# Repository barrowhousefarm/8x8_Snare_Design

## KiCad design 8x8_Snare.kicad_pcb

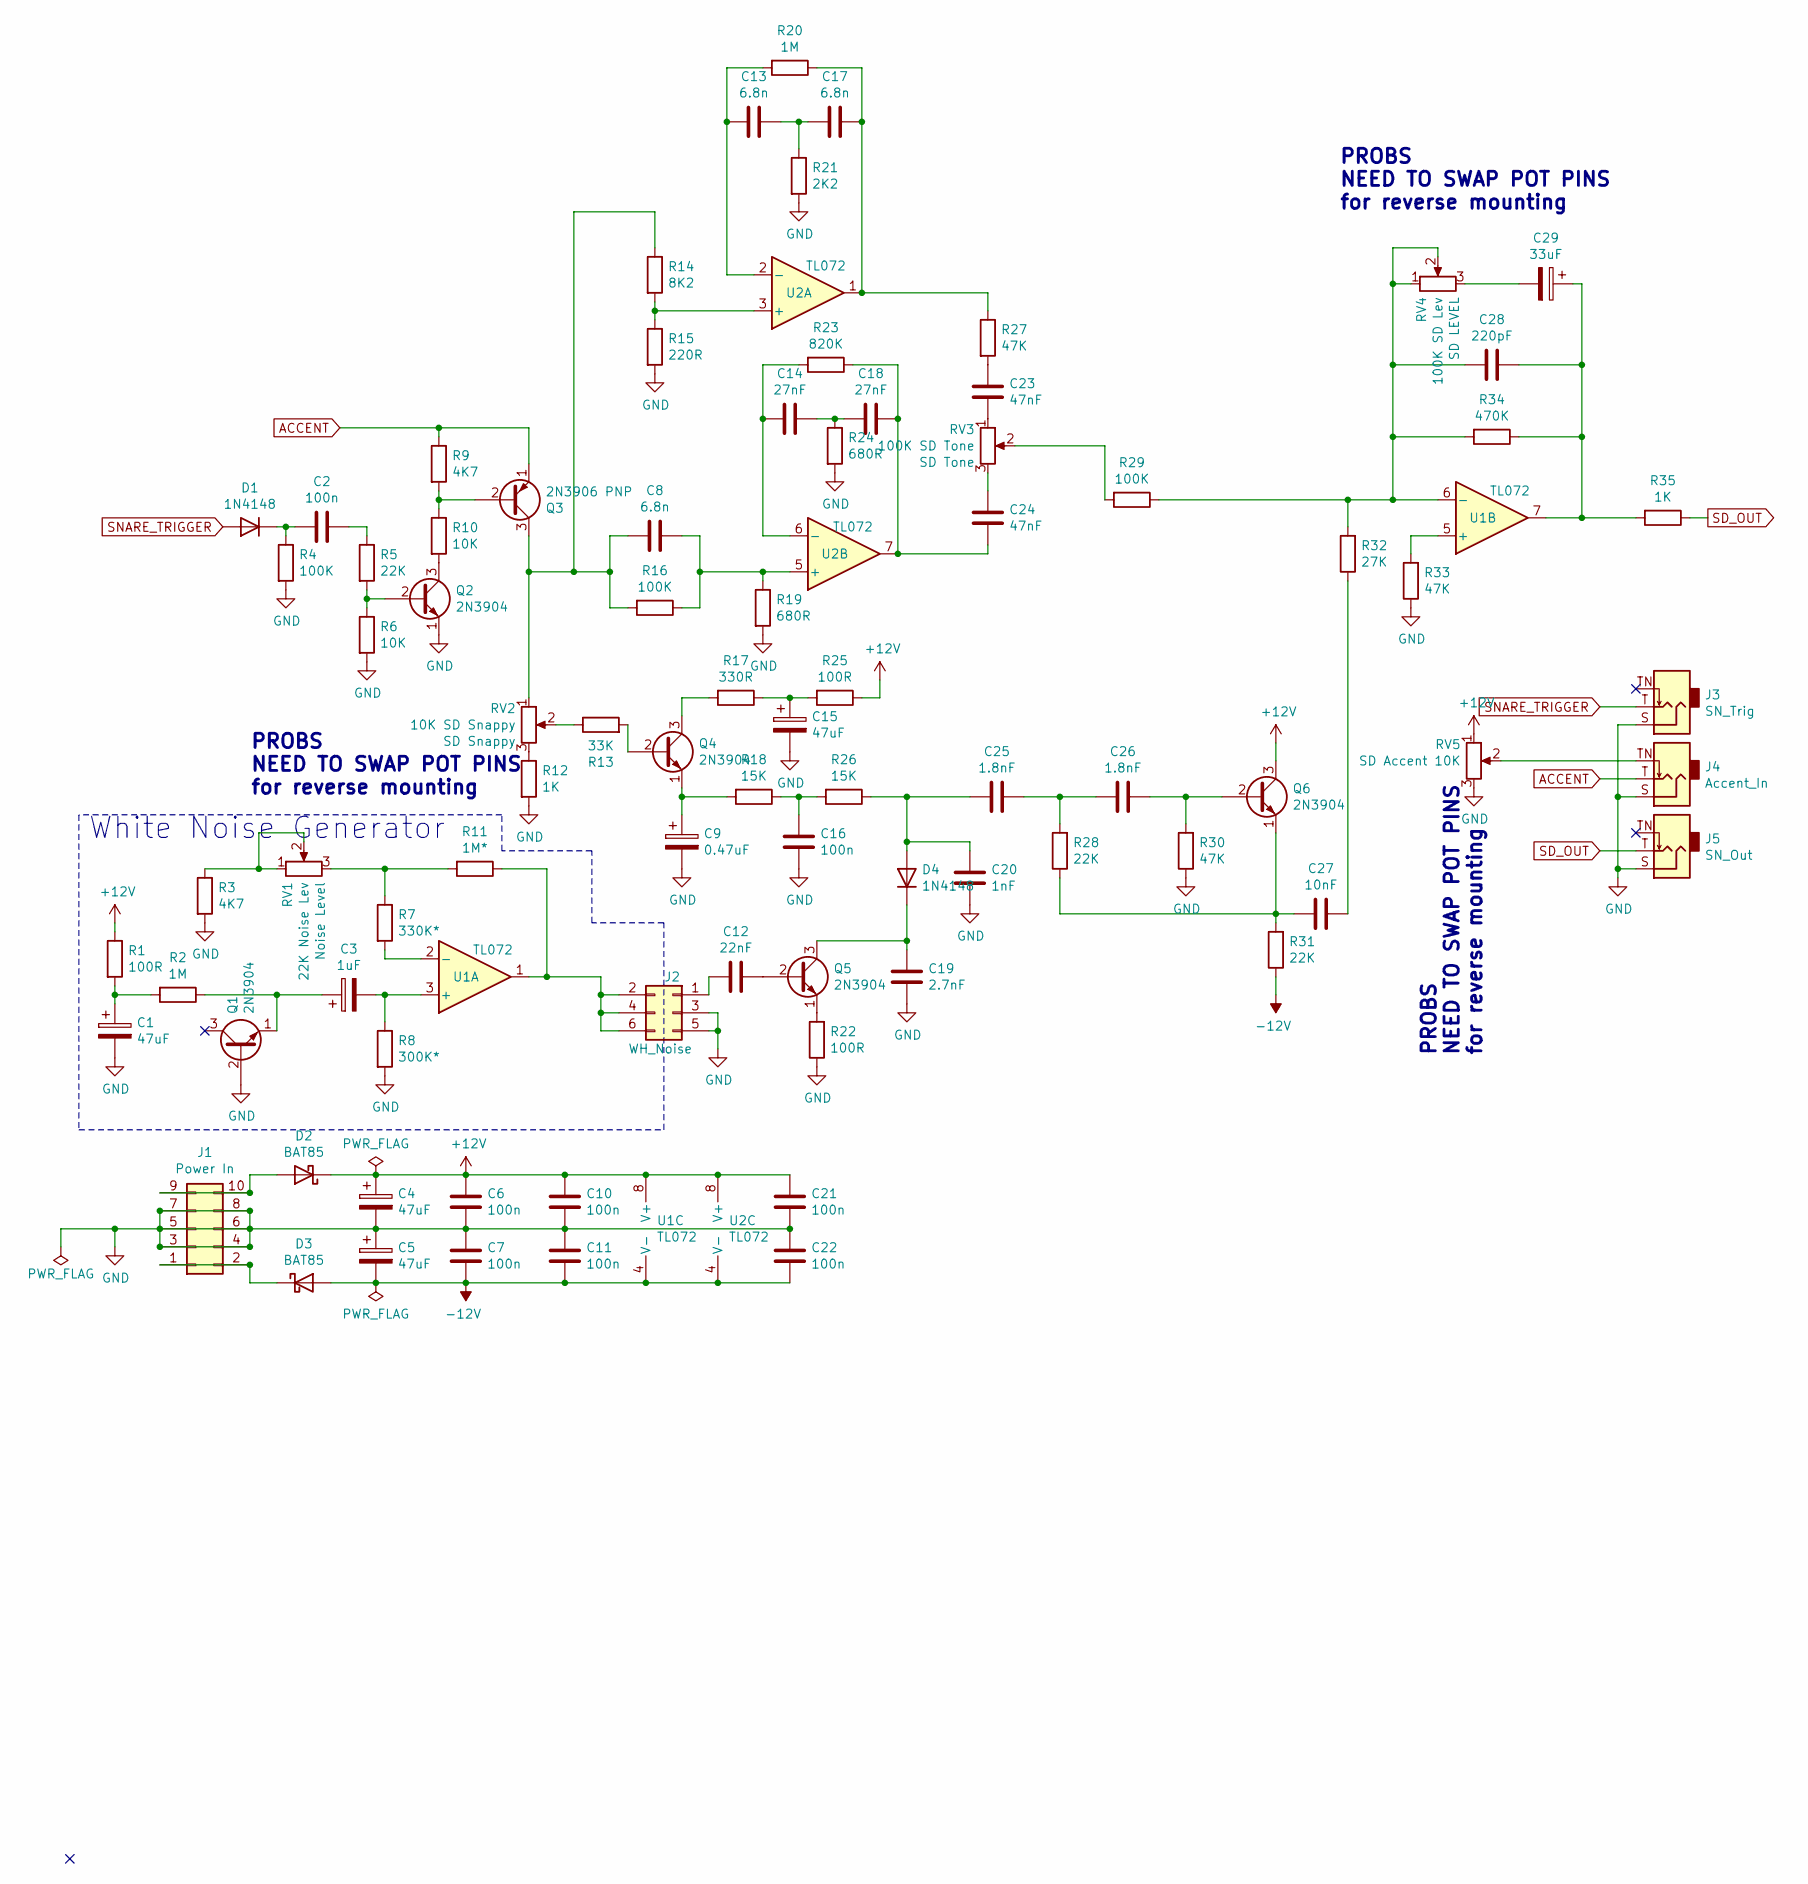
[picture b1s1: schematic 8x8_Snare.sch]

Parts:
C1, C4, C5, C15: 47uF; CP_Radial_D6.3mm_P2.50mm
C2, C6, C7, C10, C11, C16, C21, C22: 100n; C_1206_3216Metric_Pad1.33x1.80mm_HandSolder
C3: 1uF; CP_Radial_D5.0mm_P2.00mm
C8, C13, C17: 6.8n; C_Disc_D5.0mm_W2.5mm_P2.50mm
C9: 0.47uF; CP_Radial_D5.0mm_P2.00mm
C12: 22nF; C_Disc_D5.0mm_W2.5mm_P2.50mm
C14, C18: 27nF; C_Disc_D5.0mm_W2.5mm_P2.50mm
C19: 2.7nF; C_Disc_D5.0mm_W2.5mm_P2.50mm
C20: 1nF; C_Disc_D5.0mm_W2.5mm_P2.50mm
C23, C24: 47nF; C_Disc_D5.0mm_W2.5mm_P2.50mm
C25, C26: 1.8nF; C_Disc_D5.0mm_W2.5mm_P2.50mm
C27: 10nF; C_1812_4532Metric_Pad1.57x3.40mm_HandSolder
C28: 220pF; C_Disc_D5.0mm_W2.5mm_P2.50mm
C29: 33uF; CP_Radial_D6.3mm_P2.50mm
D1, D4: 1N4148; D_MiniMELF_Handsoldering
D2, D3: BAT85; D_MiniMELF_Handsoldering
J1: Power In; IDC-Header_2x05_P2.54mm_Vertical
J2: WH_Noise; PinHeader_2x03_P2.54mm_Vertical
J3: SN_Trig; Jack_3.5mm_QingPu_WQP-PJ398SM_Vertical_CircularHoles
J4: Accent_In; Jack_3.5mm_QingPu_WQP-PJ398SM_Vertical_CircularHoles
J5: SN_Out; Jack_3.5mm_QingPu_WQP-PJ398SM_Vertical_CircularHoles
Q1, Q2, Q4, Q5, Q6: 2N3904; TO-92L_Inline_Wide
Q3: 2N3906 PNP; TO-92L_Inline_Wide
R1, R22, R25: 100R; R_1206_3216Metric_Pad1.30x1.75mm_HandSolder
R2, R20: 1M; R_1206_3216Metric_Pad1.30x1.75mm_HandSolder
R3, R9: 4K7; R_1206_3216Metric_Pad1.30x1.75mm_HandSolder
R4, R16, R29: 100K; R_1206_3216Metric_Pad1.30x1.75mm_HandSolder
R5, R28, R31: 22K; R_1206_3216Metric_Pad1.30x1.75mm_HandSolder
R6, R10: 10K; R_1206_3216Metric_Pad1.30x1.75mm_HandSolder
R7: 330K*; R_1206_3216Metric_Pad1.30x1.75mm_HandSolder
R8: 300K*; R_1206_3216Metric_Pad1.30x1.75mm_HandSolder
R11: 1M*; R_1206_3216Metric_Pad1.30x1.75mm_HandSolder
R12, R35: 1K; R_1206_3216Metric_Pad1.30x1.75mm_HandSolder
R13: 33K; R_1206_3216Metric_Pad1.30x1.75mm_HandSolder
R14: 8K2; R_1206_3216Metric_Pad1.30x1.75mm_HandSolder
R15: 220R; R_1206_3216Metric_Pad1.30x1.75mm_HandSolder
R17: 330R; R_1206_3216Metric_Pad1.30x1.75mm_HandSolder
R18, R26: 15K; R_1206_3216Metric_Pad1.30x1.75mm_HandSolder
R19, R24: 680R; R_1206_3216Metric_Pad1.30x1.75mm_HandSolder
R21: 2K2; R_1206_3216Metric_Pad1.30x1.75mm_HandSolder
R23: 820K; R_1206_3216Metric_Pad1.30x1.75mm_HandSolder
R27, R30, R33: 47K; R_1206_3216Metric_Pad1.30x1.75mm_HandSolder
R32: 27K; R_1206_3216Metric_Pad1.30x1.75mm_HandSolder
R34: 470K; R_1206_3216Metric_Pad1.30x1.75mm_HandSolder
RV1: 22K Noise Lev; Potentiometer_Bourns_3296X_Horizontal
RV2: 10K SD Snappy; Potentiometer_Alpha_RD901F-40-00D_Single_Vertical
RV3: 100K SD Tone; Potentiometer_Alpha_RD901F-40-00D_Single_Vertical
RV4: 100K SD Lev; Potentiometer_Alpha_RD901F-40-00D_Single_Vertical
RV5: SD Accent 10K; Potentiometer_Alpha_RD901F-40-00D_Single_Vertical
U1, U2: TL072; DIP-8_W7.62mm_LongPads

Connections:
+12V: C4.1, C6.2, C10.2, C21.2, D2.1 (K), Q6.3 (C), R1.1, R25.1, RV5.1, U1.8 (V+), U2.8 (V+)
-12V: C5.2, C7.1, C11.1, C22.1, D3.2 (A), R31.1, U1.4 (V-), U2.4 (V-)
ACCENT: J4.T, Q3.1 (E), R9.1
GND: C1.2, C4.2, C5.1, C6.1, C7.2, C9.2, C10.1, C11.2, C15.2, C16.2, C19.2, C20.2, C21.1, C22.2, J1.3, J1.4, J1.5, J1.6, J1.7, J1.8, J2.3, J2.5, J3.S, J4.S, J5.S, Q1.2 (B), Q2.1 (E), R3.2, R4.2, R6.2, R8.2, R12.2, R15.2, R19.2, R21.2, R22.1, R24.2, R30.1, R33.1, RV5.3
unnamed: C1.1, R1.2, R2.2
unnamed: C2.1, R5.1
unnamed: C2.2, D1.1 (K), R4.1
unnamed: C3.1, Q1.1 (E), R2.1
unnamed: C3.2, R8.1, U1.3 (+)
unnamed: C8.1, R16.1, R19.1, U2.5 (+)
unnamed: C8.2, Q3.3 (C), R14.1, R16.2, RV2.1
unnamed: C9.1, Q4.1 (E), R18.2
unnamed: C12.1, Q5.2 (B)
unnamed: C12.2, J2.1
unnamed: C13.1, C17.2, R21.1
unnamed: C13.2, R20.2, U2.2 (-)
unnamed: C14.1, C18.2, R24.1
unnamed: C14.2, R23.2, U2.6 (-)
unnamed: C15.1, R17.1, R25.2
unnamed: C16.1, R18.1, R26.2
unnamed: C17.1, R20.1, R27.1, U2.1
unnamed: C18.1, C24.1, R23.1, U2.7
unnamed: C19.1, D4.1 (K), Q5.3 (C)
unnamed: C20.1, C25.2, D4.2 (A), R26.1
unnamed: C23.1, RV3.1
unnamed: C23.2, R27.2
unnamed: C24.2, RV3.3
unnamed: C25.1, C26.2, R28.2
unnamed: C26.1, Q6.2 (B), R30.2
unnamed: C27.1, R32.1
unnamed: C27.2, Q6.1 (E), R28.1, R31.2
unnamed: C28.1, C29.1, R34.1, R35.2, U1.7
unnamed: C28.2, R29.1, R32.2, R34.2, RV4.1, RV4.2, U1.6 (-)
unnamed: C29.2, RV4.3
unnamed: D2.2 (A), J1.9, J1.10
unnamed: D3.1 (K), J1.1, J1.2
unnamed: J2.2, J2.4, J2.6, R11.1, U1.1
unnamed: J4.TN, RV5.2
unnamed: Q2.2 (B), R5.2, R6.1
unnamed: Q2.3 (C), R10.2
unnamed: Q3.2 (B), R9.2, R10.1
unnamed: Q4.2 (B), R13.2
unnamed: Q4.3 (C), R17.2
unnamed: Q5.1 (E), R22.2
unnamed: R3.1, RV1.1, RV1.2
unnamed: R7.2, U1.2 (-)
unnamed: R7.1, R11.2, RV1.3
unnamed: R12.1, RV2.3
unnamed: R13.1, RV2.2
unnamed: R14.2, R15.1, U2.3 (+)
unnamed: R29.2, RV3.2
unnamed: R33.2, U1.5 (+)
SD_OUT: J5.T, R35.1
SNARE_TRIGGER: D1.2 (A), J3.T

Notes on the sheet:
White Noise Generator
PROBS NEED TO SWAP POT PINS for reverse mounting

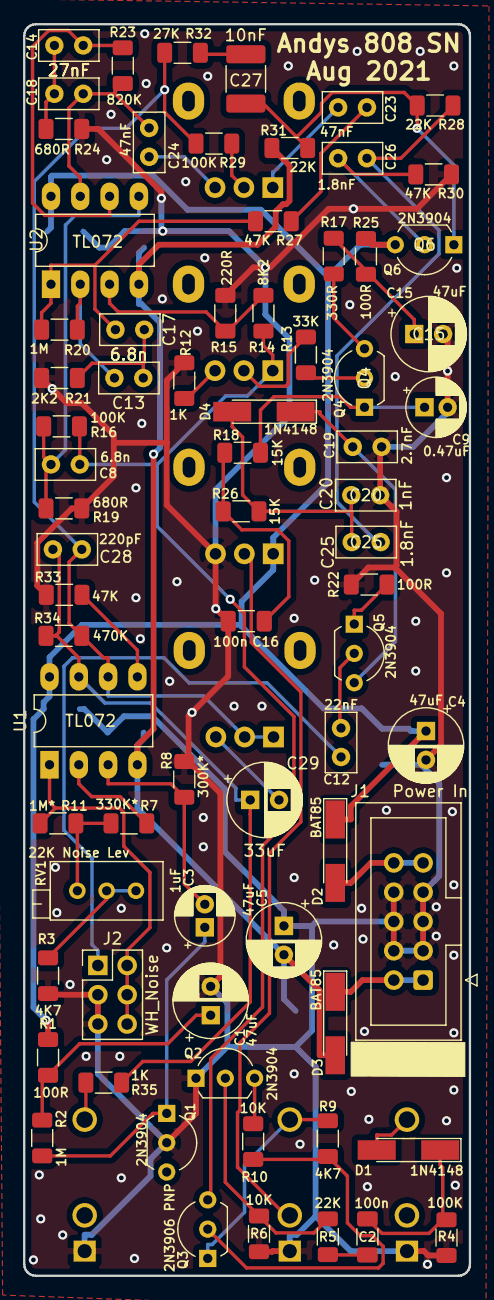
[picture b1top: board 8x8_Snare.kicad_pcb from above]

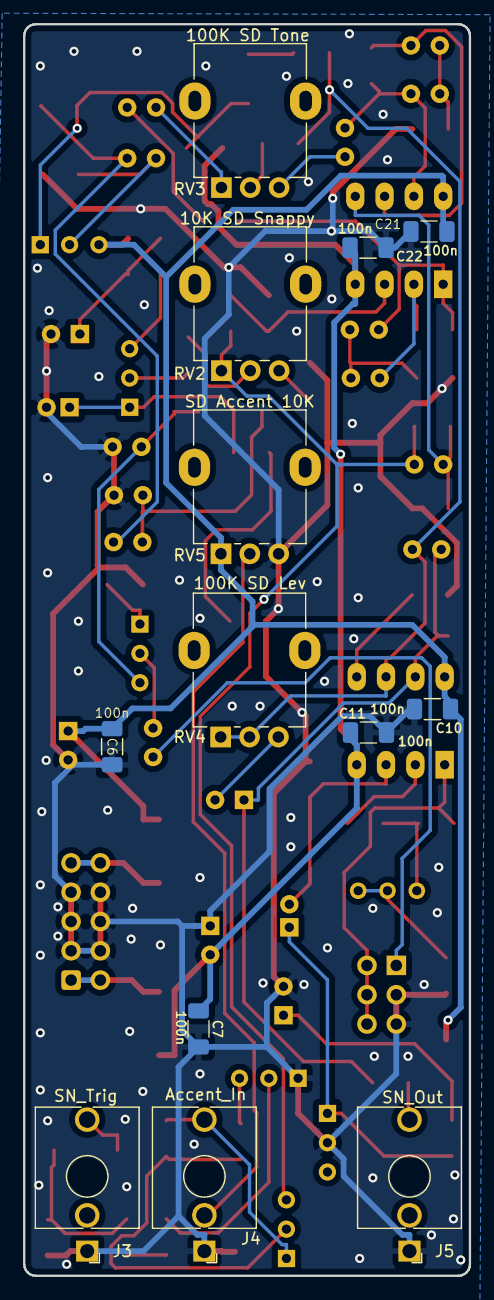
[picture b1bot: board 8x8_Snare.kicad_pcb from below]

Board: 2 copper layers, 38.6 x 108.5 mm, 86 parts (13 on the bottom side), 54 nets.

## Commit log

2023-12-29 inital upload
2023-12-29 initial upload
2024-10-25 added front panel svg for lasering
